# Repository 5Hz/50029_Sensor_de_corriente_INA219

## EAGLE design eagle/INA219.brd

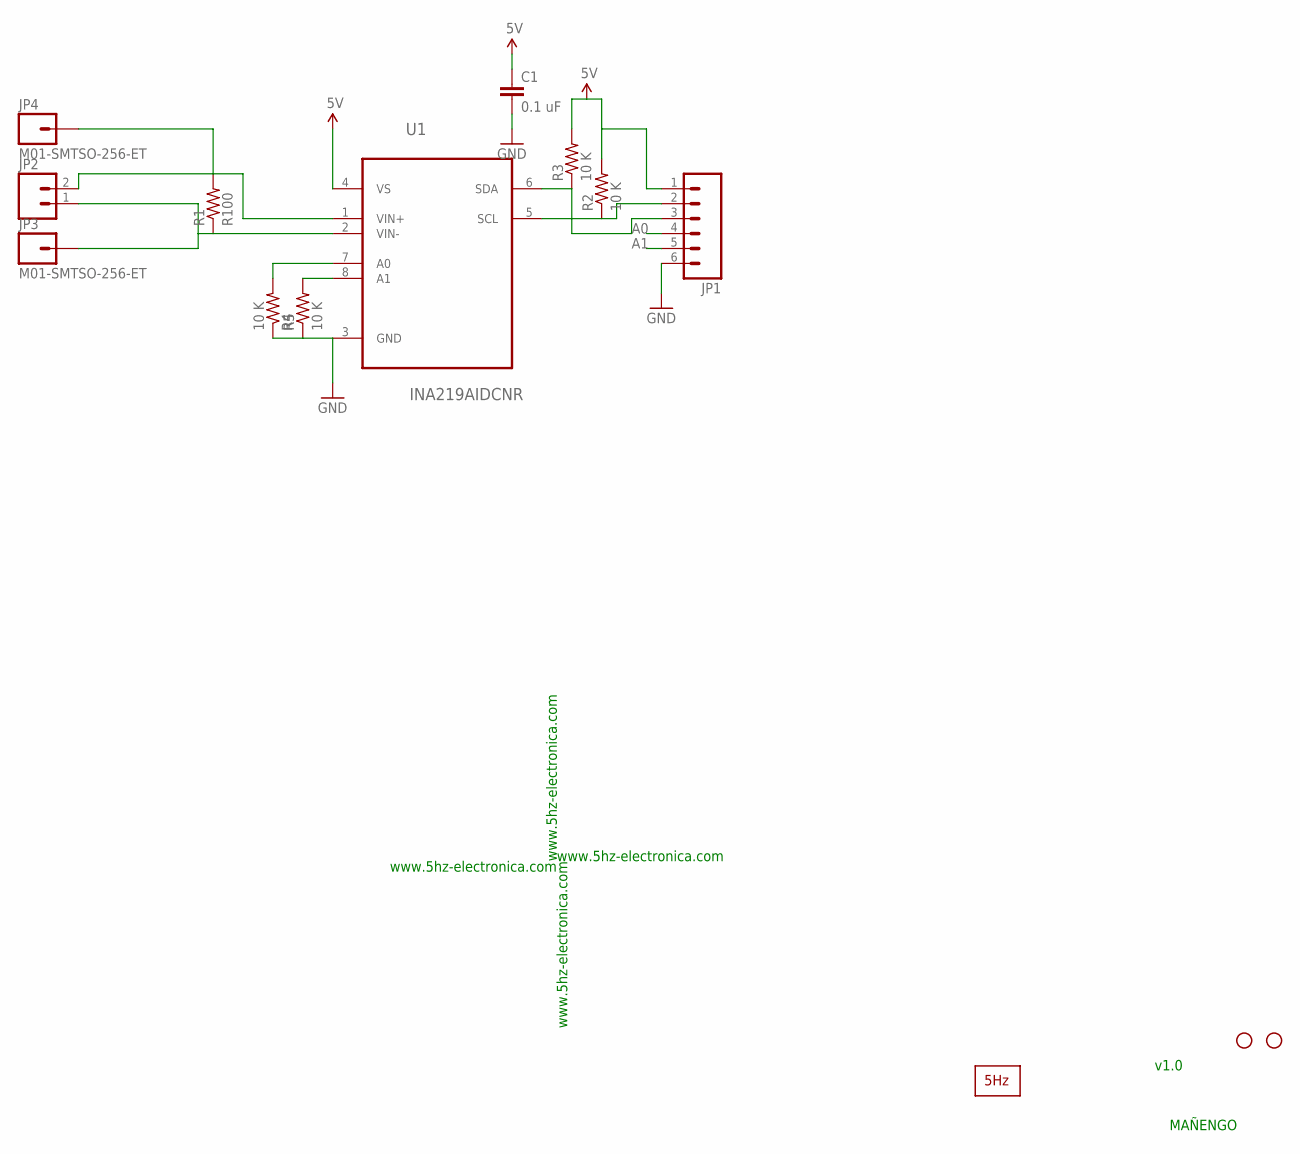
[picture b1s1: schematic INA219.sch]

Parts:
C1: 0.1 uF; 0603-CAP
JP1: M06SIP; 1X06
JP2: M023.5MM-NO_SILK; SCREWTERMINAL-3.5MM-2-NS
JP3, JP4: M01-SMTSO-256-ET; SMTSO-256-ET
JP5, JP6: STAND-OFF
R1: R100; R2512
R2, R3, R4, R5: 10 K; 0603-RES
U1: INA219AIDCNR; SOT65P280X145-8N
U$5: LOGO2_SILK5MM; LOGO2_5MM

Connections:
5V: C1.1, JP1.1, R2.2, R3.2, U1.4 (VS)
A0: JP1.4, R4.2, U1.7 (A0)
A1: JP1.5, R5.2, U1.8 (A1)
GND: C1.2, JP1.6, R4.1, R5.1, U1.3 (GND)
unnamed: JP2.2, JP4.P$1, R1.2, U1.1 (VIN+)
unnamed: JP2.1, JP3.P$1, R1.1, U1.2 (VIN-)
SCL: JP1.2, R2.1, U1.5 (SCL)
SDA: JP1.3, R3.1, U1.6 (SDA)

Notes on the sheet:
MAÑENGO
www.5hz-electronica.com
v1.0

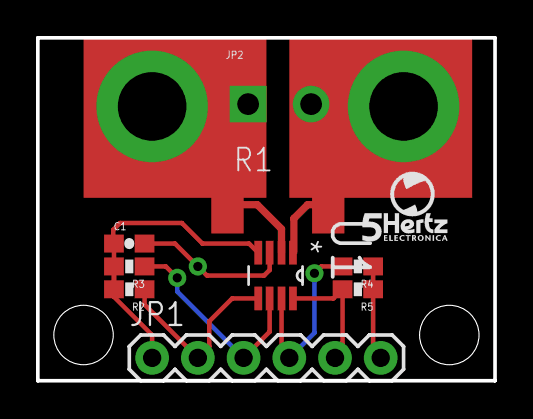
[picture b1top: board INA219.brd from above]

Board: 2 copper layers, 25.4 x 19.1 mm, 14 parts (0 on the bottom side), 8 nets.

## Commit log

2014-01-15 Creación

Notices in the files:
parts and their libraries:
SparkFun: Licensing: CC v3.0 Share-Alike You are welcome to use this library for commercial purposes.
